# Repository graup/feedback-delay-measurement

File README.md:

# Feedback Delay Measurement Instrument

This repository holds all source code and design files for my bachelor thesis: "Development and Evaluation of an Arduino-based Feedback Delay Measurement Instrument" (Paul Grau, 2016)

## Contents

* [Thesis full text](http://graycoding.com/publications/2016_BA_Thesis.pdf) (PDF)
* [PCB layout](./pcb/) (Eagle schematic and board)
* [Measurement program](./arduino/measure.ino) (Arduino sketch)
* [How to](./HOWTO.md)

## See also
* [Author's homepage](http://graycoding.com/publications/)

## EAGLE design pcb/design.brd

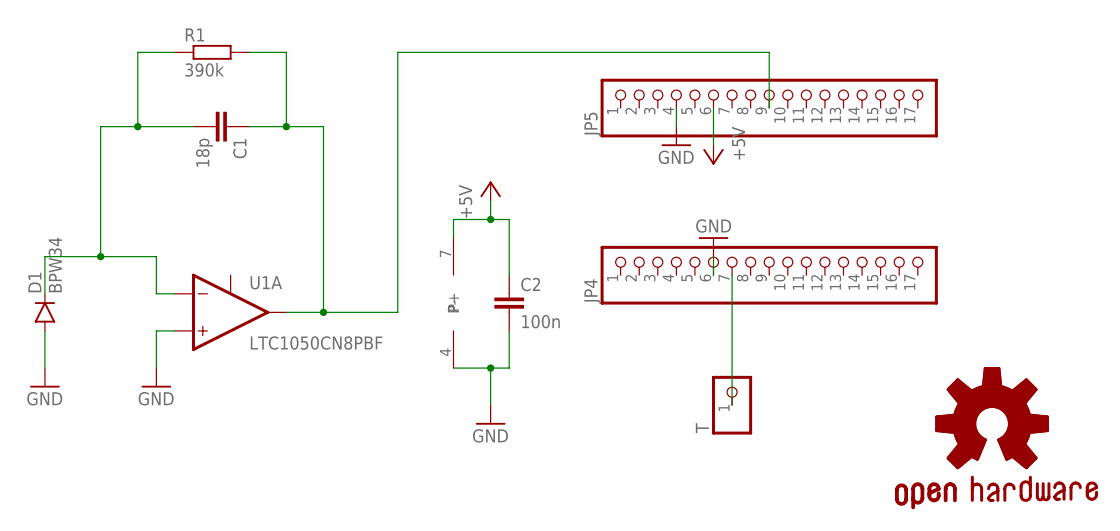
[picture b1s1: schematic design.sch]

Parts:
C1: 18p; C025-025X050
C2: 100n; C025-025X050
D1: BPW34
GOLD_ORB_SM1: OSHWLOGO_GOLD_ORB_SM; OSHW2
JP4, JP5: PINHD-1X17; 1X17
R1: 390k; 0207/2V
T: PINHD-1X1; 1X01
U1: LTC1050CN8PBF; DIP254P762X508-8

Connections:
+5V: C2.1, JP5.6, U1.7 (P+)
GND: C2.2, D1.P$1 (A), JP4.6, JP5.4, U1.3 (IN+), U1.4 (P-)
unnamed: C1.2, D1.P$2 (C), R1.1, U1.2 (IN-)
unnamed: C1.1, JP5.9, R1.2, U1.6 (OUT)
unnamed: JP4.7, T.1

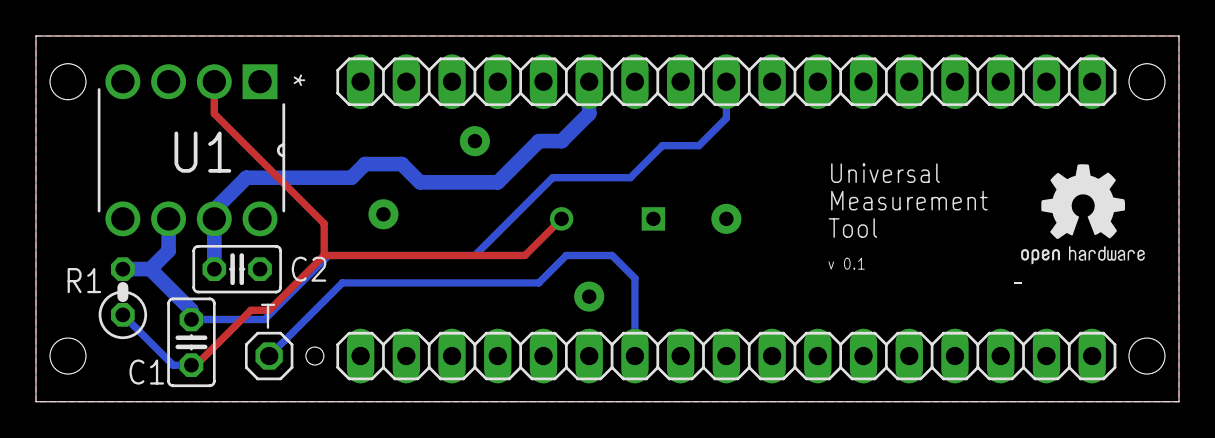
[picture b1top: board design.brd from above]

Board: 2 copper layers, 63.5 x 20.3 mm, 9 parts (1 on the bottom side), 5 nets.

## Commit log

2016-03-20 init repo
2016-03-23 added thesis files

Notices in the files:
parts and their libraries:
SparkFun-Sensors: Licensing: Creative Commons ShareAlike 4.0 International - https://creativecommons.org/licenses/by-sa/4.0
